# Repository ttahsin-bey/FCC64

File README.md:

# FCC64
Final Chess Card - Forum64 Edition

Current Design:

Recent Prototype:

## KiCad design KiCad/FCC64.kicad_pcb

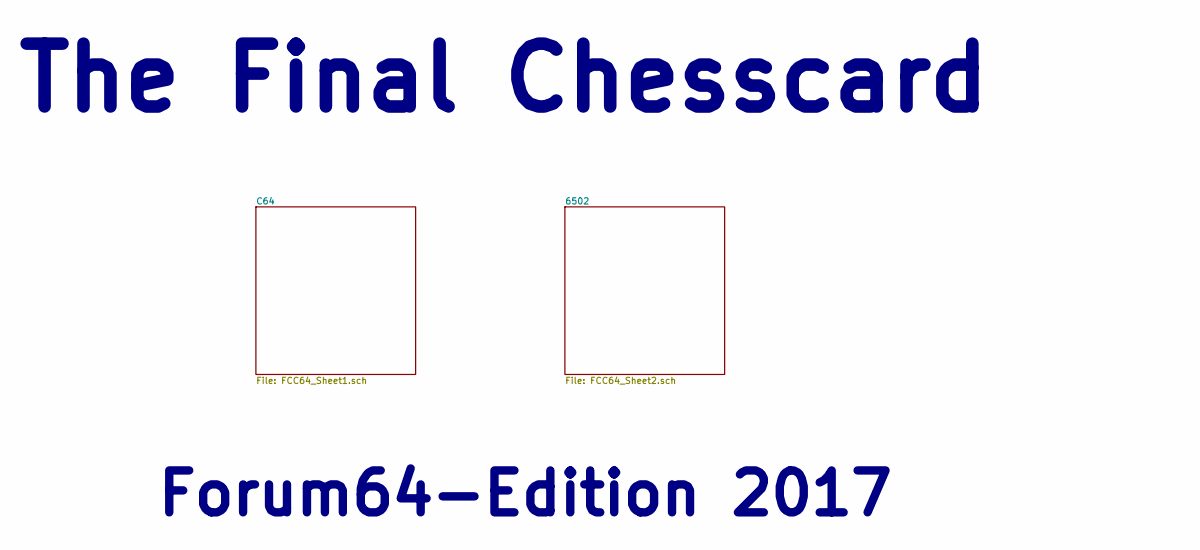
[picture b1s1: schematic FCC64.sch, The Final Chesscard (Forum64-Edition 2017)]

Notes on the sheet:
The Final Chesscard
Forum64-Edition 2017

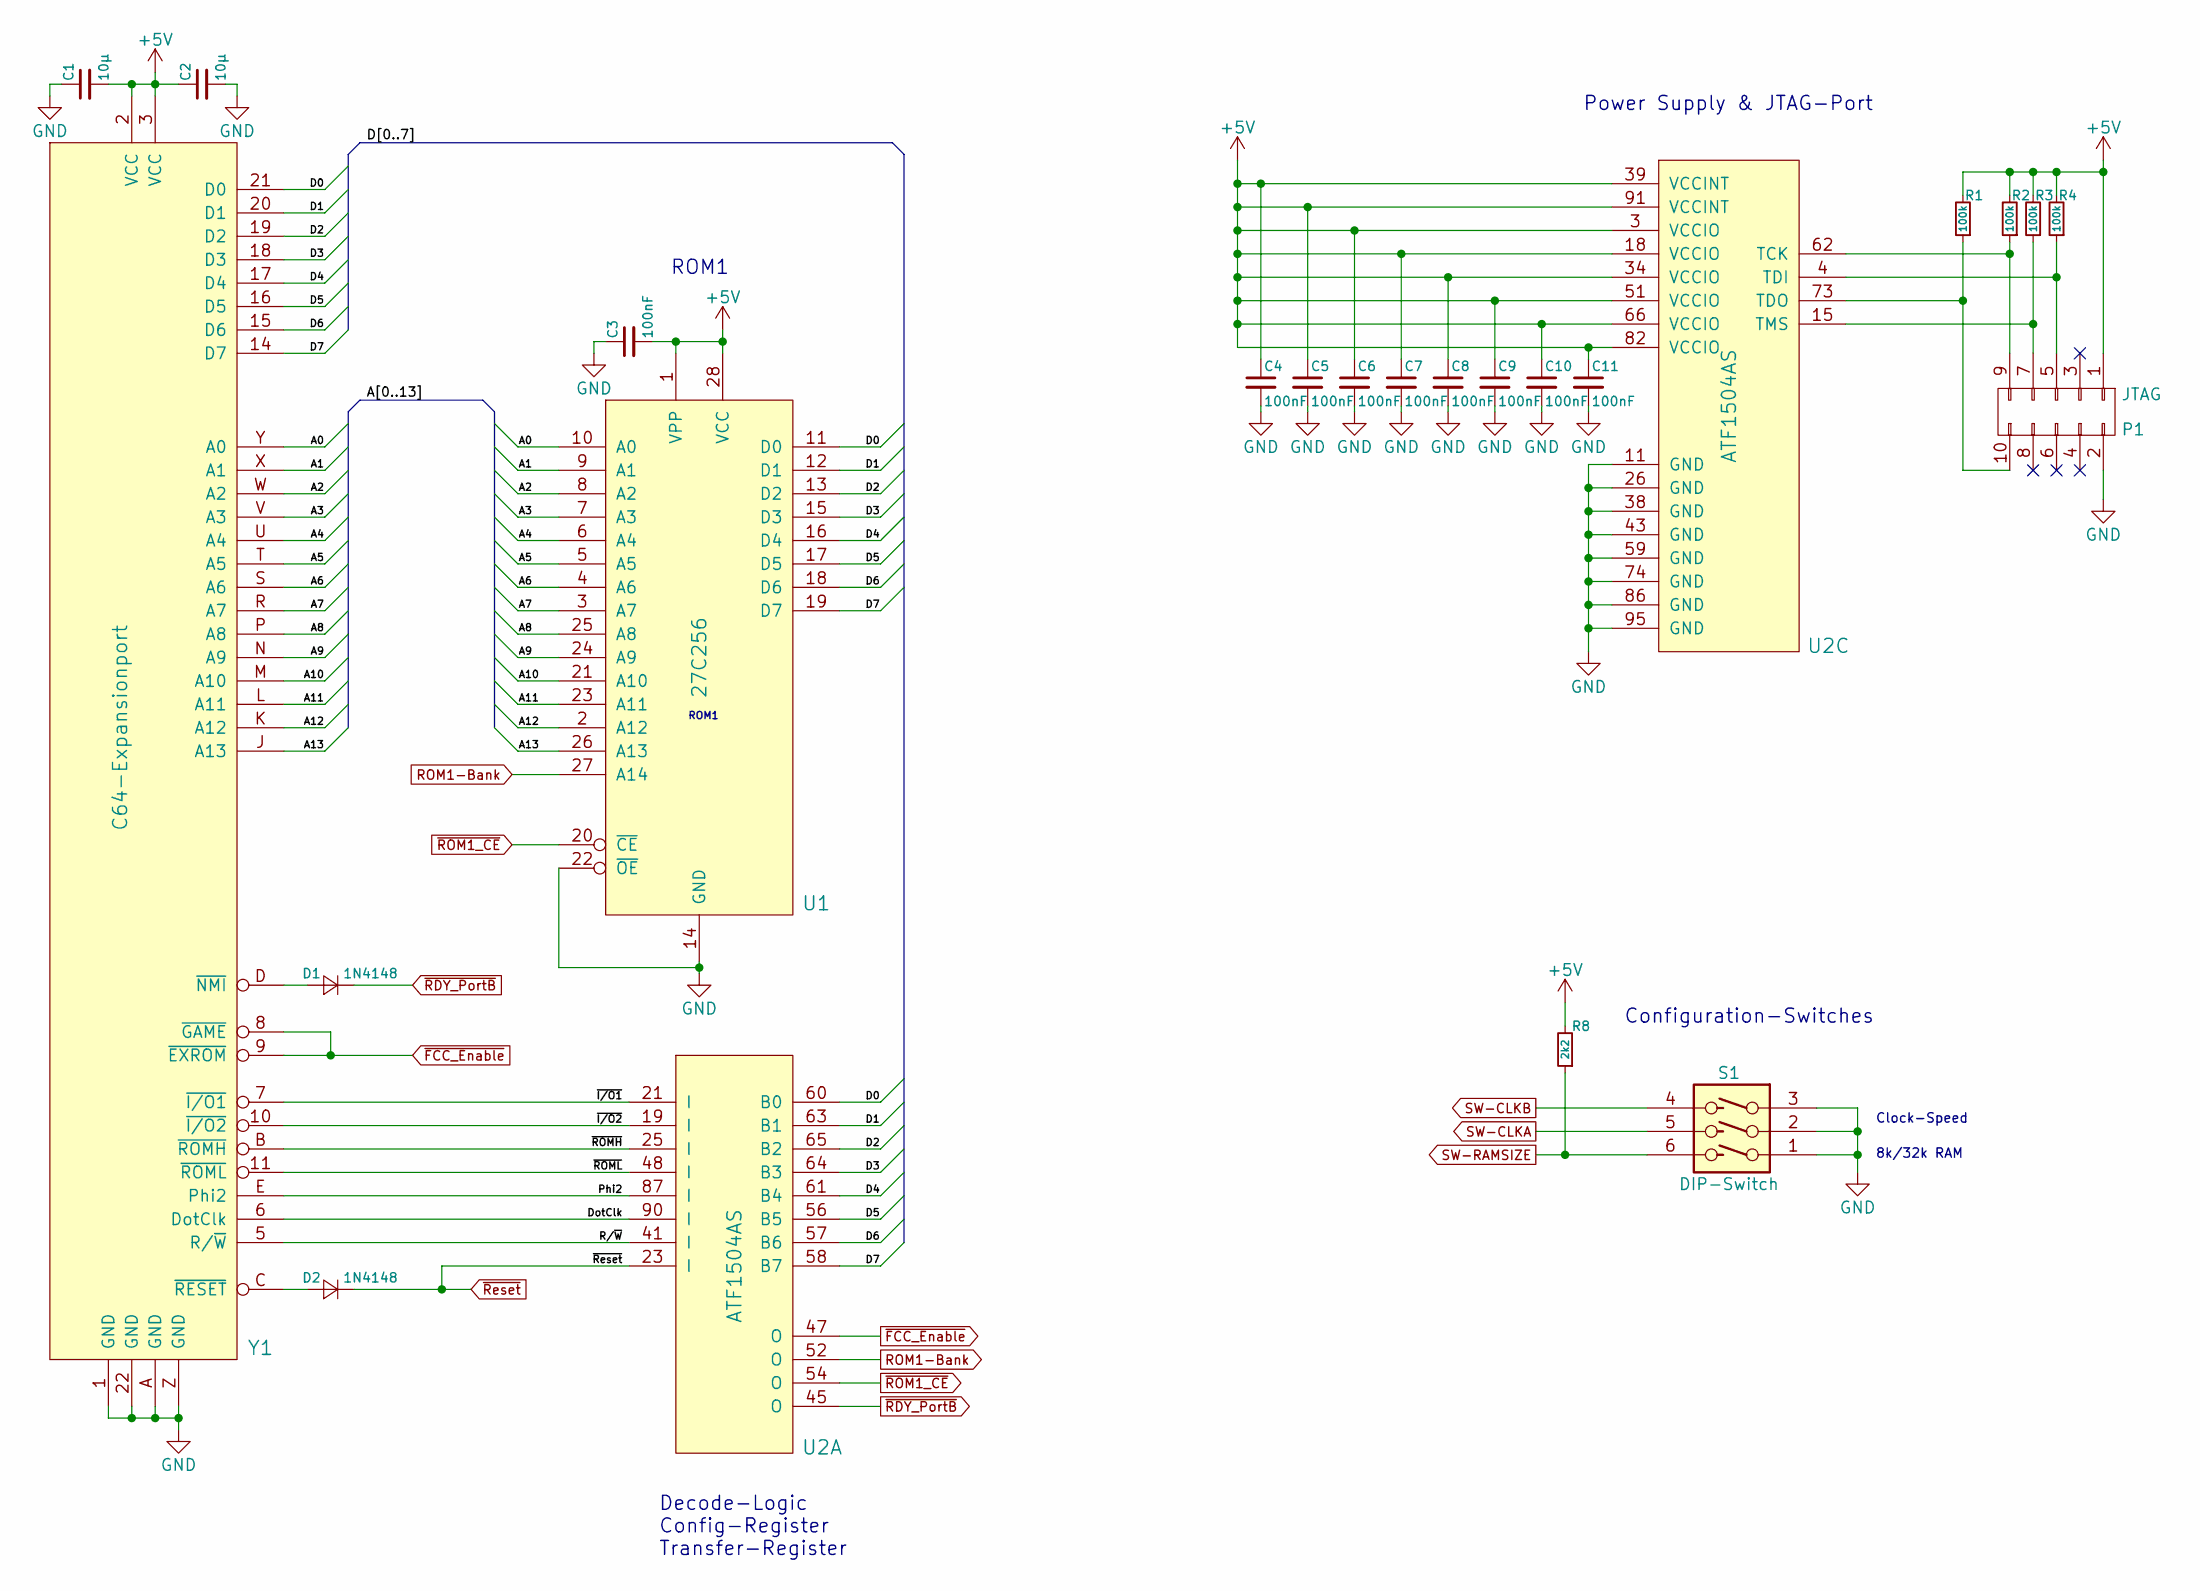
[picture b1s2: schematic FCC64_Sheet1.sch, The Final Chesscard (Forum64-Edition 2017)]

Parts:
C1, C2: 10µ; TTB_C1206
C3, C4, C5, C6, C7, C8, C9, C10, C11: 100nF; TTB_C0603
D1, D2: 1N4148; TTB_D0603
P1: JTAG; Pin_Header_Straight_2x05_Pitch2.00mm
R1, R2, R3, R4: 100k; TTB_R0603
R8: 2k2; TTB_R0603
S1: DIP-Switch; TTB_DIPSwitch3
U1: 27C256; TTB_DIL28
U2: ATF1504AS; TTB_TQFP100
Y1: C64-Expansionport; TTB_C64_Expansionport

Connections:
+5V: C1.2, C2.1, C3.2, C4.1, C5.1, C6.1, C7.1, C8.1, C9.1, C10.1, C11.1, P1.1, R1.2, R2.2, R3.2, R4.2, R8.2, U1.1 (VPP), U1.28 (VCC), U2.3 (VCCIO), U2.18 (VCCIO), U2.34 (VCCIO), U2.39 (VCCINT), U2.51 (VCCIO), U2.66 (VCCIO), U2.82 (VCCIO), U2.91 (VCCINT), Y1.2 (VCC), Y1.3 (VCC); also elsewhere on the board
/C64/A0: U1.10 (A0), Y1.Y (A0)
/C64/A1: U1.9 (A1), Y1.X (A1)
/C64/A2: U1.8 (A2), Y1.W (A2)
/C64/A3: U1.7 (A3), Y1.V (A3)
/C64/A4: U1.6 (A4), Y1.U (A4)
/C64/A5: U1.5 (A5), Y1.T (A5)
/C64/A6: U1.4 (A6), Y1.S (A6)
/C64/A7: U1.3 (A7), Y1.R (A7)
/C64/A8: U1.25 (A8), Y1.P (A8)
/C64/A9: U1.24 (A9), Y1.N (A9)
/C64/A10: U1.21 (A10), Y1.M (A10)
/C64/A11: U1.23 (A11), Y1.L (A11)
/C64/A12: U1.2 (A12), Y1.K (A12)
/C64/A13: U1.26 (A13), Y1.J (A13)
/C64/D0: U1.11 (D0), U2.60 (B0), Y1.21 (D0)
/C64/D1: U1.12 (D1), U2.63 (B1), Y1.20 (D1)
/C64/D2: U1.13 (D2), U2.65 (B2), Y1.19 (D2)
/C64/D3: U1.15 (D3), U2.64 (B3), Y1.18 (D3)
/C64/D4: U1.16 (D4), U2.61 (B4), Y1.17 (D4)
/C64/D5: U1.17 (D5), U2.56 (B7), Y1.16 (D5)
/C64/D6: U1.18 (D6), U2.57 (B6), Y1.15 (D6)
/C64/D7: U1.19 (D7), U2.58 (B5), Y1.14 (D7)
/C64/DotClk: U2.90 (I), Y1.6 (DotClk)
/C64/Phi2: U2.87 (I), Y1.E (Phi2)
/C64/R/~W: U2.41 (I), Y1.5 (R/~W)
/C64/~I/O1: U2.21 (I), Y1.7 (~I/O1)
/C64/~I/O2: U2.19 (I), Y1.10 (~I/O2)
/C64/~ROMH: U2.25 (I), Y1.B (~ROMH)
/C64/~ROML: U2.48 (I), Y1.11 (~ROML)
GND: C1.1, C2.2, C3.1, C4.2, C5.2, C6.2, C7.2, C8.2, C9.2, C10.2, C11.2, P1.2, S1.1, S1.2, S1.3, U1.14 (GND), U1.22 (~OE), U2.11 (GND), U2.26 (GND), U2.38 (GND), U2.43 (GND), U2.59 (GND), U2.74 (GND), U2.86 (GND), U2.95 (GND), Y1.1 (GND), Y1.22 (GND), Y1.A (GND), Y1.Z (GND); also elsewhere on the board
unnamed: D1.2 (A), Y1.D (~NMI)
unnamed: D2.2 (A), Y1.C (~RESET)
unnamed: P1.5, R4.1, U2.4 (TDI)
unnamed: P1.7, R3.1, U2.15 (TMS)
unnamed: P1.9, R2.1, U2.62 (TCK)
unnamed: P1.10, R1.1, U2.73 (TDO)
ROM1-Bank: U1.27 (A14), U2.52 (O)
SW-CLKA: S1.5; also elsewhere on the board
SW-CLKB: S1.4; also elsewhere on the board
SW-RAMSIZE: R8.1, S1.6; also elsewhere on the board
~FCC_Enable: U2.47 (O), Y1.8 (~GAME), Y1.9 (~EXROM)
~RDY_PortB: D1.1 (K), U2.45 (O)
~ROM1_CE: U1.20 (~CE), U2.54 (O)
~Reset: D2.1 (K), U2.23 (I); also elsewhere on the board

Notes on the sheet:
ROM1
Decode-Logic Config-Register Transfer-Register
Power Supply & JTAG-Port
Configuration-Switches
8k/32k RAM
Clock-Speed

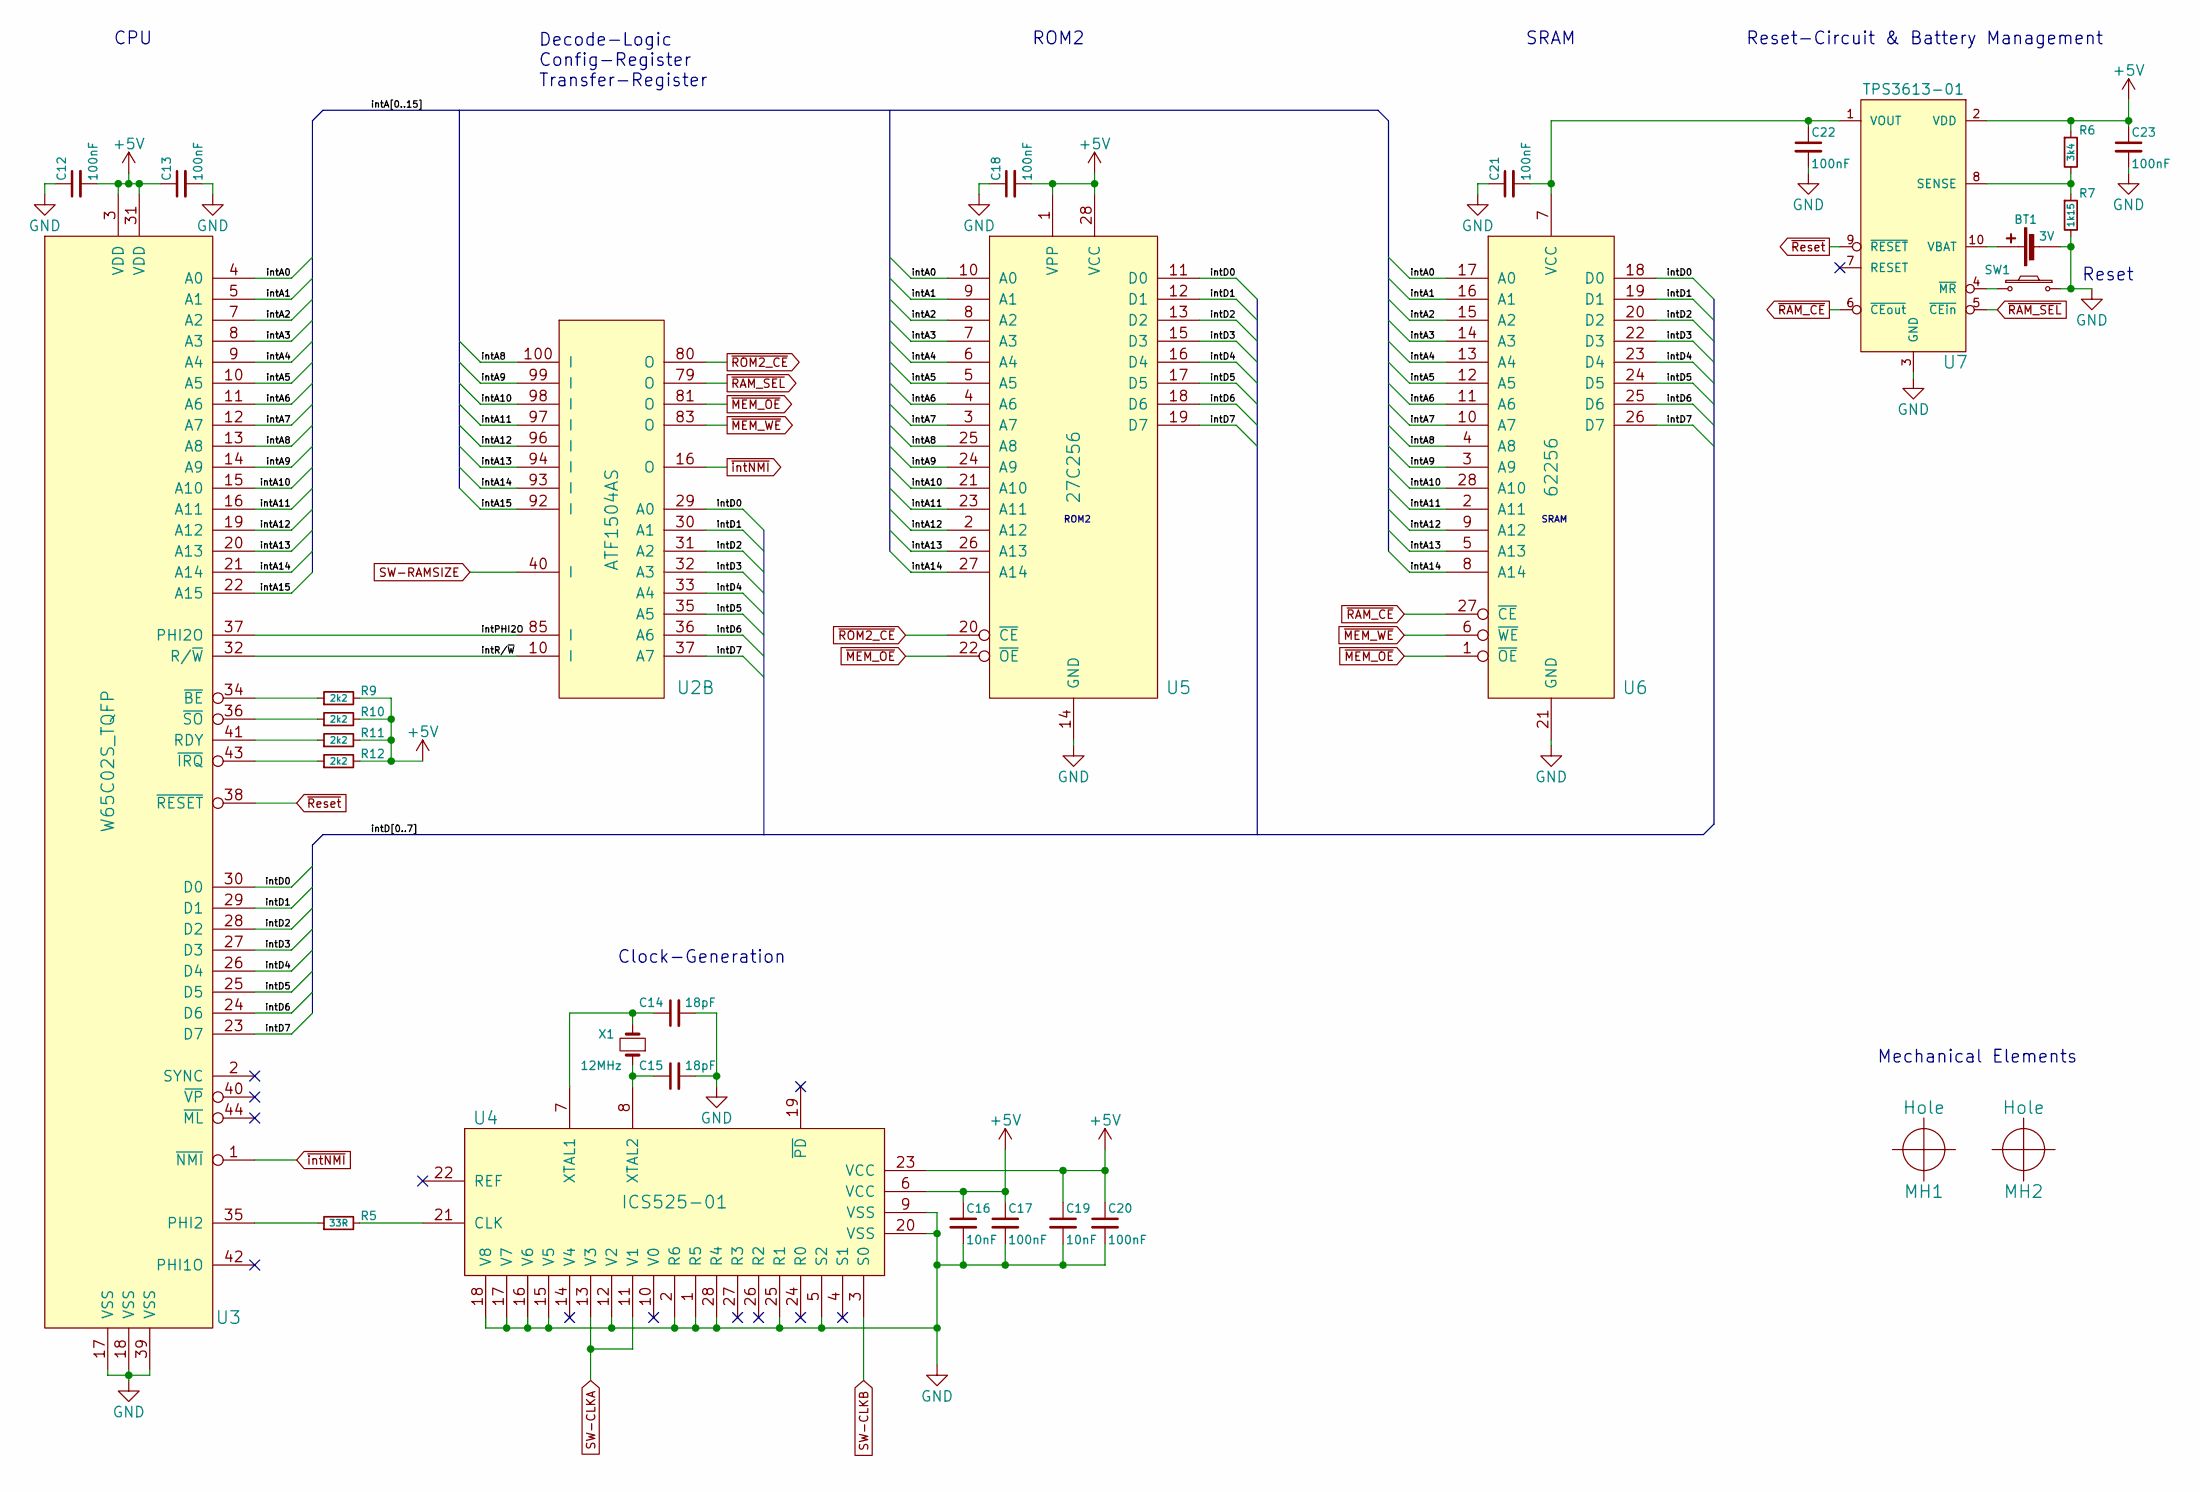
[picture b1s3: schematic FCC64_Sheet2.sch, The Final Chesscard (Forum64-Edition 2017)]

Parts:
BT1: 3V; TTB_Batteriehalter
C12, C13, C17, C18, C20, C21, C22, C23: 100nF; TTB_C0603
C14, C15: 18pF; TTB_C0603wide
C16, C19: 10nF; TTB_C0603
MH1: Hole; TTB_Hole4,8mm
MH2: Hole; TTB_Hole3,1mm
R5: 33R; TTB_R0603
R6: 3k4; TTB_R0603
R7: 1k15; TTB_R0603
R9, R10, R11, R12: 2k2; TTB_R0603
SW1: Reset; TTB_Pushbutton_3305
U2: ATF1504AS; TTB_TQFP100
U3: W65C02S_TQFP; TTB_W65C02
U4: ICS525-01; TTB_TSSOP28
U5: 27C256; TTB_DIL28
U6: 62256; TTB_TSOP1_28
U7: TPS3613-01; TTB_MSOP10
X1: 12MHz; TTB_7A

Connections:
+5V: C12.2, C13.1, C16.1, C17.1, C18.2, C19.1, C20.1, C23.1, R6.1, R9.2, R10.2, R11.2, R12.2, U3.3 (VDD), U3.31 (VDD), U4.6 (VCC), U4.23 (VCC), U5.1 (VPP), U5.28 (VCC), U7.2 (VDD); also elsewhere on the board
/6502/intA0: U3.4 (A0), U5.10 (A0), U6.17 (A0)
/6502/intA1: U3.5 (A1), U5.9 (A1), U6.16 (A1)
/6502/intA2: U3.7 (A2), U5.8 (A2), U6.15 (A2)
/6502/intA3: U3.8 (A3), U5.7 (A3), U6.14 (A3)
/6502/intA4: U3.9 (A4), U5.6 (A4), U6.13 (A4)
/6502/intA5: U3.10 (A5), U5.5 (A5), U6.12 (A5)
/6502/intA6: U3.11 (A6), U5.4 (A6), U6.11 (A6)
/6502/intA7: U3.12 (A7), U5.3 (A7), U6.10 (A7)
/6502/intA8: U2.100 (I), U3.13 (A8), U5.25 (A8), U6.4 (A8)
/6502/intA9: U2.99 (I), U3.14 (A9), U5.24 (A9), U6.3 (A9)
/6502/intA10: U2.98 (I), U3.15 (A10), U5.21 (A10), U6.28 (A10)
/6502/intA11: U2.97 (I), U3.16 (A11), U5.23 (A11), U6.2 (A11)
/6502/intA12: U2.96 (I), U3.19 (A12), U5.2 (A12), U6.9 (A12)
/6502/intA13: U2.94 (I), U3.20 (A13), U5.26 (A13), U6.5 (A13)
/6502/intA14: U2.93 (I), U3.21 (A14), U5.27 (A14), U6.8 (A14)
/6502/intA15: U2.92 (I), U3.22 (A15)
/6502/intD0: U2.29 (A0), U3.30 (D0), U5.11 (D0), U6.18 (D0)
/6502/intD1: U2.30 (A1), U3.29 (D1), U5.12 (D1), U6.19 (D1)
/6502/intD2: U2.31 (A2), U3.28 (D2), U5.13 (D2), U6.20 (D2)
/6502/intD3: U2.32 (A3), U3.27 (D3), U5.15 (D3), U6.22 (D3)
/6502/intD4: U2.33 (A4), U3.26 (D4), U5.16 (D4), U6.23 (D4)
/6502/intD5: U2.35 (A5), U3.25 (D5), U5.17 (D5), U6.24 (D5)
/6502/intD6: U2.36 (A6), U3.24 (D6), U5.18 (D6), U6.25 (D6)
/6502/intD7: U2.37 (A7), U3.23 (D7), U5.19 (D7), U6.26 (D7)
/6502/intPHI2O: U2.85 (I), U3.37 (PHI2O)
/6502/intR/~W: U2.10 (I), U3.32 (R/~W)
GND: BT1.2 (-), C12.1, C13.2, C14.2, C15.2, C16.2, C17.2, C18.1, C19.2, C20.2, C21.1, C22.2, C23.2, R7.2, SW1.1, U3.17 (VSS), U3.18 (VSS), U3.39 (VSS), U4.1 (R5), U4.2 (R6), U4.5 (S2), U4.9 (VSS), U4.12 (V2), U4.15 (V5), U4.16 (V6), U4.17 (V7), U4.18 (V8), U4.20 (VSS), U4.25 (R1), U4.28 (R4), U5.14 (GND), U6.21 (GND), U7.3 (GND); also elsewhere on the board
unnamed: BT1.1 (+), U7.10 (VBAT)
unnamed: C14.1, U4.7 (XTAL1), X1.2
unnamed: C15.1, U4.8 (XTAL2), X1.1
unnamed: C21.2, C22.1, U6.7 (VCC), U7.1 (VOUT)
unnamed: R5.1, U3.35 (PHI2)
unnamed: R5.2, U4.21 (CLK)
unnamed: R6.2, R7.1, U7.8 (SENSE)
unnamed: R9.1, U3.34 (~BE)
unnamed: R10.1, U3.36 (~SO)
unnamed: R11.1, U3.41 (RDY)
unnamed: R12.1, U3.43 (~IRQ)
unnamed: SW1.2, U7.4 (~MR)
SW-CLKA: U4.11 (V1), U4.13 (V3); also elsewhere on the board
SW-CLKB: U4.3 (S0); also elsewhere on the board
SW-RAMSIZE: U2.40 (I); also elsewhere on the board
~MEM_OE: U2.81 (O), U5.22 (~OE), U6.1 (~OE)
~MEM_WE: U2.83 (O), U6.6 (~WE)
~RAM_CE: U6.27 (~CE), U7.6 (~CEout)
~RAM_SEL: U2.79 (O), U7.5 (~CEin)
~ROM2_CE: U2.80 (O), U5.20 (~CE)
~Reset: U3.38 (~RESET), U7.9 (~RESET); also elsewhere on the board
~intNMI: U2.16 (O), U3.1 (~NMI)

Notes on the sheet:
ROM2
SRAM
CPU
Clock-Generation
Reset-Circuit & Battery Management
Decode-Logic Config-Register Transfer-Register
Reset
Mechanical Elements

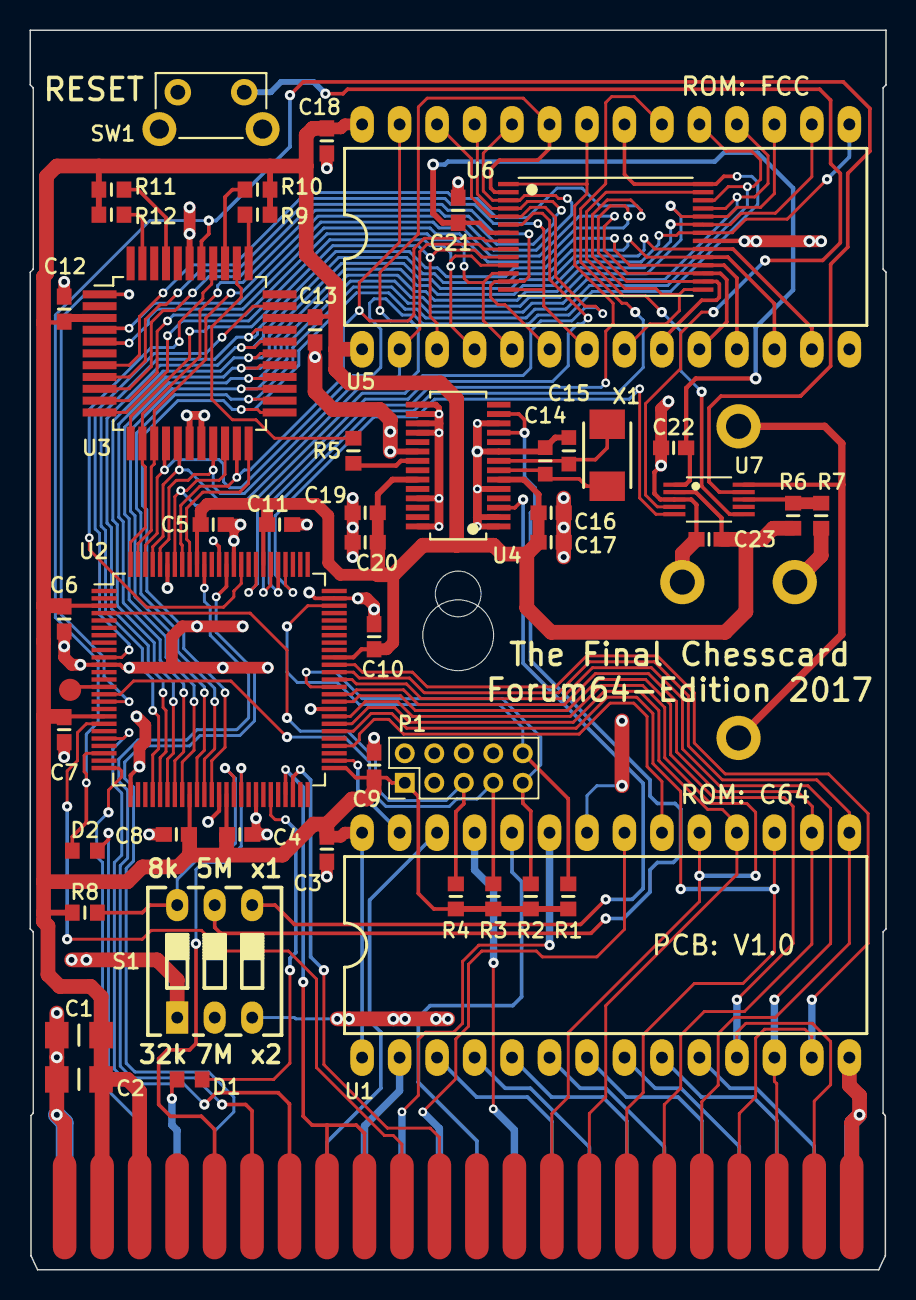
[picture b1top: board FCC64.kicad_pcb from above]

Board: 2 copper layers, 58.0 x 84.0 mm, 52 parts (1 on the bottom side), 89 nets.

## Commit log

2017-06-15 Layoutdaten hochgeladen
2017-06-15 CPLD initial commit
2017-06-15 Platzhalter für ROM-Files hochgeladen
2017-07-02 Erste bootfähige Version
2017-07-03 Anpassungen bezüglich positiver Taktflanke
2017-07-04 Nummerierung der Datenleitungen am C64-Expansionport korrigiert.
2017-07-04 weitere Anpassungen
2017-07-05 Direction of Labels at IC3A and IC3D changed to "outgoing"
2017-07-10 Various issues solved:
    * QFP44-Footprint for W65C02 corrected
    * FCC-On/Off deleted
    * new battery supervisor ic TPS6513-01
    * Battery Holder corrected
    * Signals D5 and D7 to CPLD swapped
2017-07-10 Images removed
2017-07-10 Images added
2017-07-29 Tidying up for initial batch
2017-09-03 Width of Slot-Connector reduced by 0,1mm
2017-09-03 Small visual improvements
2017-09-03 Bill of Material created
2017-09-23 PCB Thickness added
2020-03-31 Logic equations updated. Cartridge now fully working at 5 MHz with crom 1.3 and brom 1.5.
